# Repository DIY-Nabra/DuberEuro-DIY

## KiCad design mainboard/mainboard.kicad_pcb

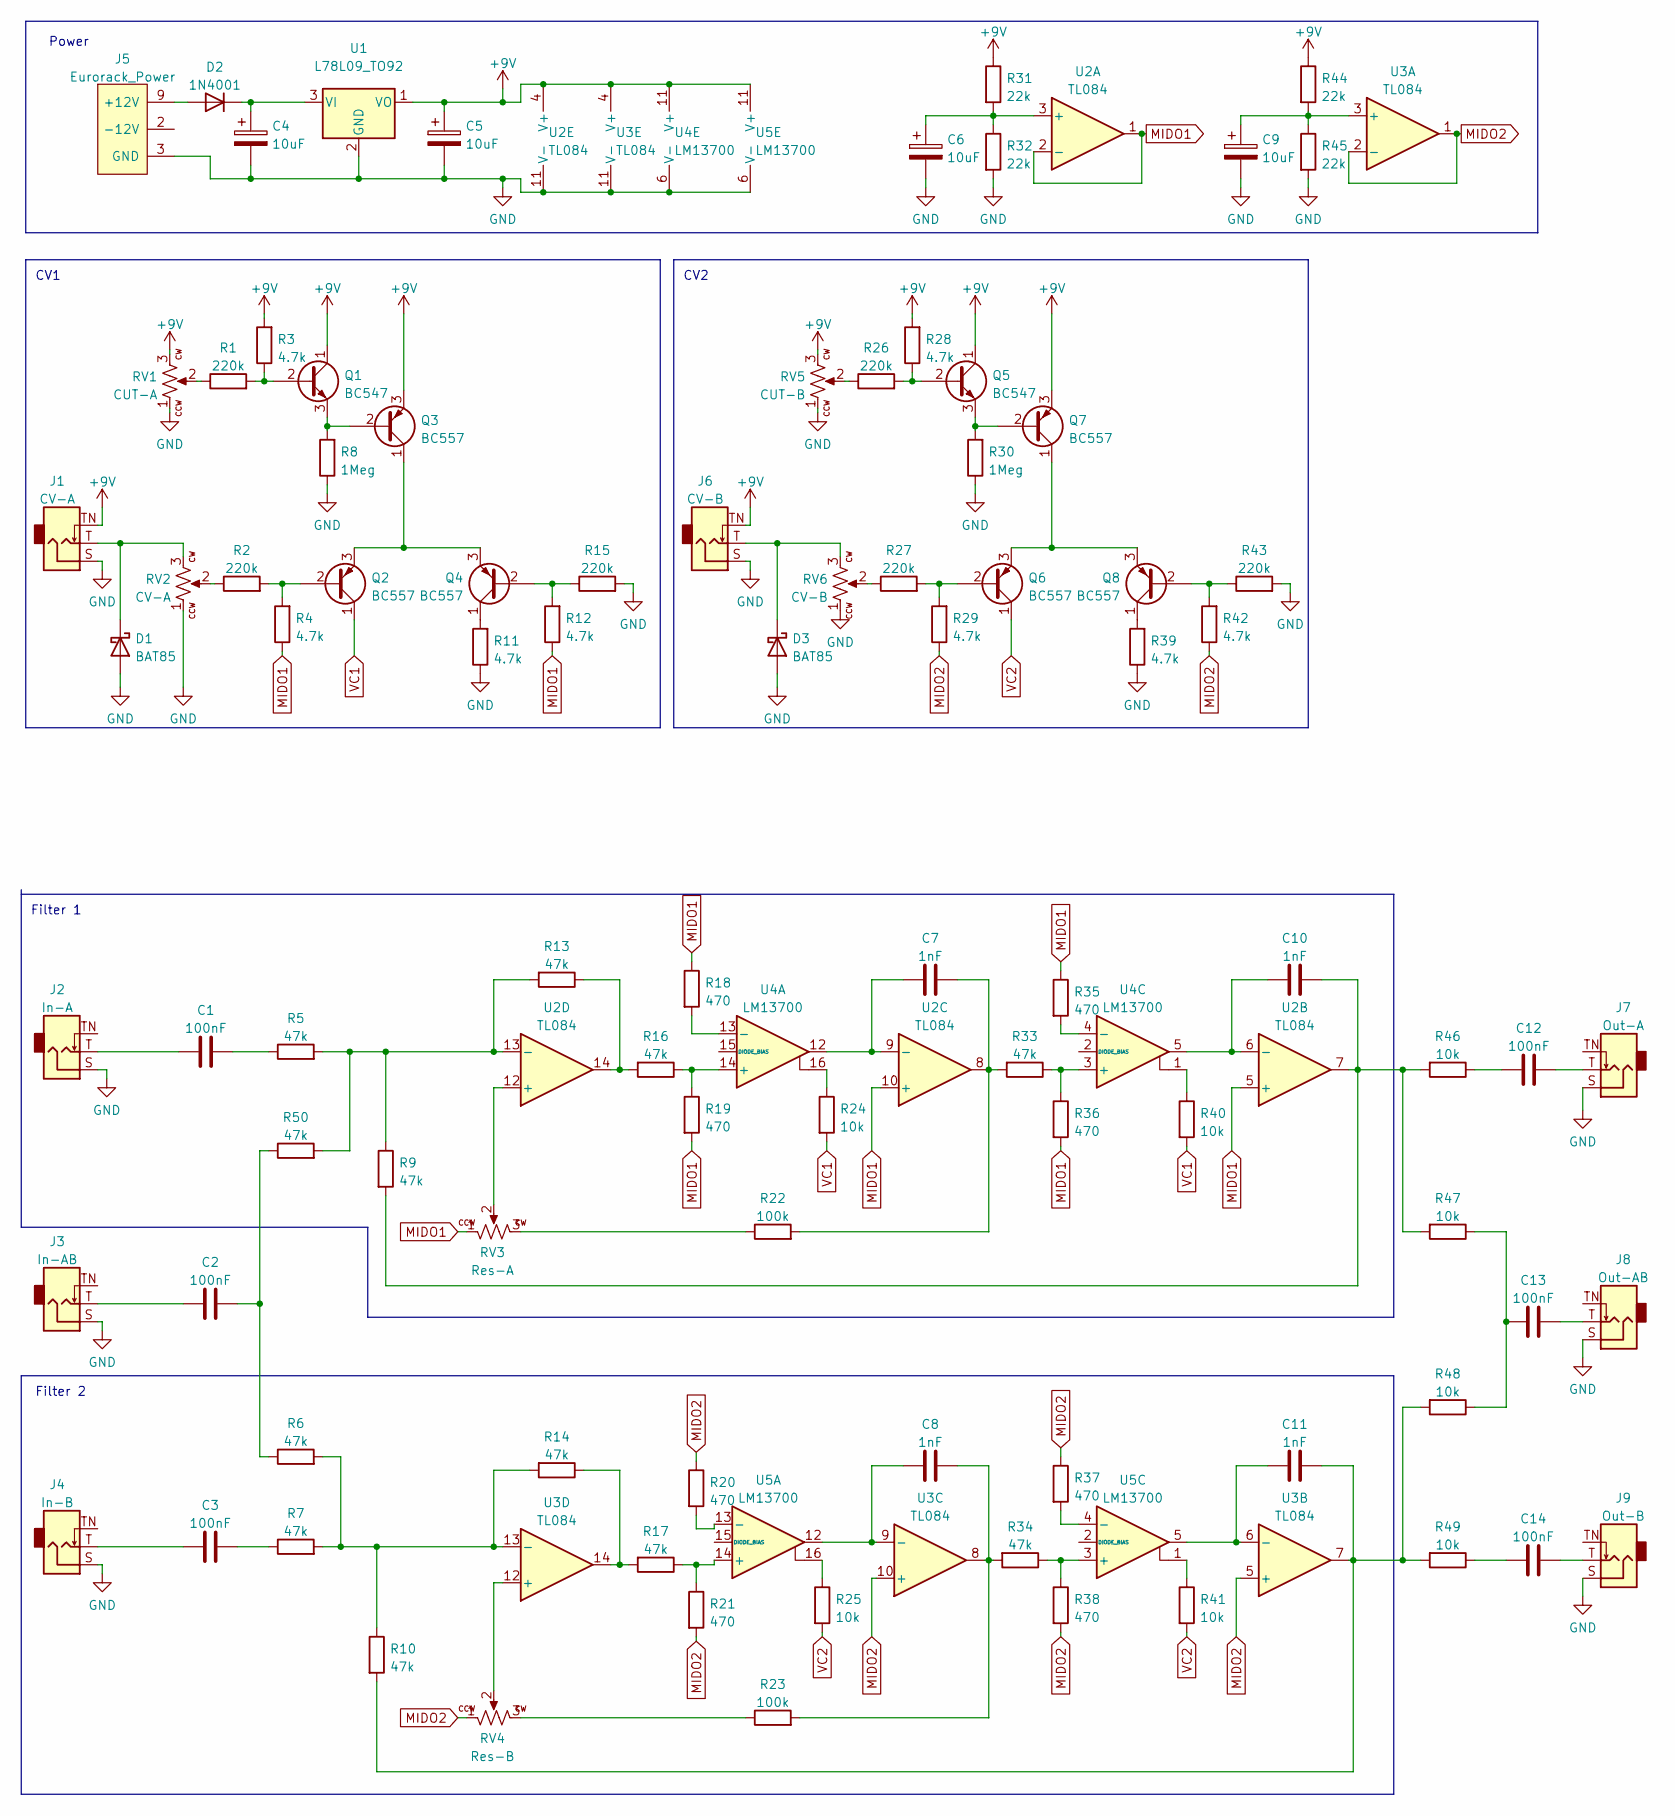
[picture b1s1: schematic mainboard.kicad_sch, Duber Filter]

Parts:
C1, C2, C3, C12, C13, C14: 100nF; C_Axial_L3.8mm_D2.6mm_P7.50mm_Horizontal
C4, C5, C6, C9: 10uF; CP_Radial_D5.0mm_P2.50mm
C7, C8, C10, C11: 1nF; C_Disc_D5.0mm_W2.5mm_P5.00mm
D1, D3: BAT85; D_DO-35_SOD27_P7.62mm_Horizontal
D2: 1N4001; D_DO-41_SOD81_P10.16mm_Horizontal
J1: CV-A; AudioJack_WQP518MA; MPN WQP-WQP518MA
J2: In-A; AudioJack_WQP518MA; MPN WQP-WQP518MA
J3: In-AB; AudioJack_WQP518MA; MPN WQP-WQP518MA
J4: In-B; AudioJack_WQP518MA; MPN WQP-WQP518MA
J5: Eurorack_Power; Eurorack_Power_2x5_Shrouded; MPN 302-S101
J6: CV-B; AudioJack_WQP518MA; MPN WQP-WQP518MA
J7: Out-A; AudioJack_WQP518MA; MPN WQP-WQP518MA
J8: Out-AB; AudioJack_WQP518MA; MPN WQP-WQP518MA
J9: Out-B; AudioJack_WQP518MA; MPN WQP-WQP518MA
Q1, Q5: BC547; TO-92_Inline
Q2, Q3, Q4, Q6, Q7, Q8: BC557; TO-92_Inline
R1, R2, R15, R26, R27, R43: 220k; R_Axial_DIN0204_L3.6mm_D1.6mm_P7.62mm_Horizontal
R3, R4, R11, R12, R28, R29, R39, R42: 4.7k; R_Axial_DIN0204_L3.6mm_D1.6mm_P7.62mm_Horizontal
R5, R6, R7, R9, R10, R13, R14, R16, R17, R33, R34, R50: 47k; R_Axial_DIN0204_L3.6mm_D1.6mm_P7.62mm_Horizontal
R8, R30: 1Meg; R_Axial_DIN0204_L3.6mm_D1.6mm_P7.62mm_Horizontal
R18, R19, R20, R21, R35, R36, R37, R38: 470; R_Axial_DIN0204_L3.6mm_D1.6mm_P7.62mm_Horizontal
R22, R23: 100k; R_Axial_DIN0204_L3.6mm_D1.6mm_P7.62mm_Horizontal
R24, R25, R40, R41, R46, R47, R48, R49: 10k; R_Axial_DIN0204_L3.6mm_D1.6mm_P7.62mm_Horizontal
R31, R32, R44, R45: 22k; R_Axial_DIN0204_L3.6mm_D1.6mm_P7.62mm_Horizontal
RV1: CUT-A; Potentiometer_Alpha_R0904N; MPN R0904N-???? L-25KQ/LWS
RV2: CV-A; Potentiometer_Alpha_R0904N; MPN R0904N-???? L-25KQ/LWS
RV3: Res-A; Potentiometer_Alpha_R0904N; MPN R0904N-???? L-25KQ/LWS
RV4: Res-B; Potentiometer_Alpha_R0904N; MPN R0904N-???? L-25KQ/LWS
RV5: CUT-B; Potentiometer_Alpha_R0904N; MPN R0904N-???? L-25KQ/LWS
RV6: CV-B; Potentiometer_Alpha_R0904N; MPN R0904N-???? L-25KQ/LWS
U1: L78L09_TO92; TO-92_Inline
U2, U3: TL084; DIP-14_W7.62mm_Socket
U4, U5: LM13700; DIP-16_W7.62mm_Socket

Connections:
+9V: C5.1, J1.TN (Tip_normalize), J6.TN (Tip_normalize), Q1.1 (C), Q3.3 (E), Q5.1 (C), Q7.3 (E), R3.2, R28.2, R31.1, R44.1, RV1.3, RV5.3, U1.1 (VO), U2.4 (V+), U3.4 (V+), U4.11 (V+), U5.11 (V+)
GND: C4.2, C5.2, C6.2, C9.2, D1.2 (A), D3.2 (A), J1.S (Sleeve), J2.S (Sleeve), J3.S (Sleeve), J4.S (Sleeve), J5.3 (GND), J5.4 (GND), J5.5 (GND), J5.6 (GND), J5.7 (GND), J5.8 (GND), J6.S (Sleeve), J7.S (Sleeve), J8.S (Sleeve), J9.S (Sleeve), R8.1, R11.1, R15.2, R30.1, R32.2, R39.1, R43.2, R45.2, RV1.1, RV2.1, RV5.1, RV6.1, U1.2 (GND), U2.11 (V-), U3.11 (V-), U4.6 (V-), U5.6 (V-)
MIDO1: R4.1, R12.1, R18.1, R19.2, R35.1, R36.2, RV3.1, U2.1, U2.2 (-), U2.5 (+), U2.10 (+)
MIDO2: R20.1, R21.2, R29.1, R37.1, R38.2, R42.1, RV4.1, U3.1, U3.2 (-), U3.5 (+), U3.10 (+)
unnamed: C1.1, J2.T (Tip)
unnamed: C1.2, R5.1
unnamed: C2.1, J3.T (Tip)
unnamed: C2.2, R6.1, R50.1
unnamed: C3.1, J4.T (Tip)
unnamed: C3.2, R7.1
unnamed: C4.1, D2.1 (K), U1.3 (VI)
unnamed: C6.1, R31.2, R32.1, U2.3 (+)
unnamed: C7.1, U2.9 (-), U4.12
unnamed: C7.2, R22.2, R33.2, U2.8
unnamed: C8.1, U3.9 (-), U5.12
unnamed: C8.2, R23.2, R34.2, U3.8
unnamed: C9.1, R44.2, R45.1, U3.3 (+)
unnamed: C10.1, U2.6 (-), U4.5
unnamed: C10.2, R9.2, R46.2, R47.2, U2.7
unnamed: C11.1, U3.6 (-), U5.5
unnamed: C11.2, R10.2, R48.2, R49.2, U3.7
unnamed: C12.1, R46.1
unnamed: C12.2, J7.T (Tip)
unnamed: C13.1, R47.1, R48.1
unnamed: C13.2, J8.T (Tip)
unnamed: C14.1, R49.1
unnamed: C14.2, J9.T (Tip)
unnamed: D1.1 (K), J1.T (Tip), RV2.3
unnamed: D2.2 (A), J5.9 (+12V), J5.10 (+12V)
unnamed: D3.1 (K), J6.T (Tip), RV6.3
unnamed: J5.1 (-12V), J5.2 (-12V)
unnamed: Q1.2 (B), R1.2, R3.1
unnamed: Q1.3 (E), Q3.2 (B), R8.2
unnamed: Q2.2 (B), R2.2, R4.2
unnamed: Q2.3 (E), Q3.1 (C), Q4.3 (E)
unnamed: Q4.1 (C), R11.2
unnamed: Q4.2 (B), R12.2, R15.1
unnamed: Q5.2 (B), R26.2, R28.1
unnamed: Q5.3 (E), Q7.2 (B), R30.2
unnamed: Q6.2 (B), R27.2, R29.2
unnamed: Q6.3 (E), Q7.1 (C), Q8.3 (E)
unnamed: Q8.1 (C), R39.2
unnamed: Q8.2 (B), R42.2, R43.1
unnamed: R1.1, RV1.2
unnamed: R2.1, RV2.2
unnamed: R6.2, R7.2, R10.1, R14.2, U3.13 (-)
unnamed: R13.1, R16.2, U2.14
unnamed: R5.2, R9.1, R13.2, R50.2, U2.13 (-)
unnamed: R14.1, R17.2, U3.14
unnamed: R16.1, R19.1, U4.14 (+)
unnamed: R17.1, R21.1, U5.14 (+)
unnamed: R18.2, U4.13 (-)
unnamed: R20.2, U5.13 (-)
unnamed: R22.1, RV3.3
unnamed: R23.1, RV4.3
unnamed: R24.1, U4.16
unnamed: R25.1, U5.16
unnamed: R26.1, RV5.2
unnamed: R27.1, RV6.2
unnamed: R33.1, R36.1, U4.3 (+)
unnamed: R34.1, R38.1, U5.3 (+)
unnamed: R35.2, U4.4 (-)
unnamed: R37.2, U5.4 (-)
unnamed: R40.1, U4.1
unnamed: R41.1, U5.1
unnamed: RV3.2, U2.12 (+)
unnamed: RV4.2, U3.12 (+)
VC1: Q2.1 (C), R24.2, R40.2
VC2: Q6.1 (C), R25.2, R41.2

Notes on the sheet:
CV1
Filter 2
Power
Filter 1
CV2

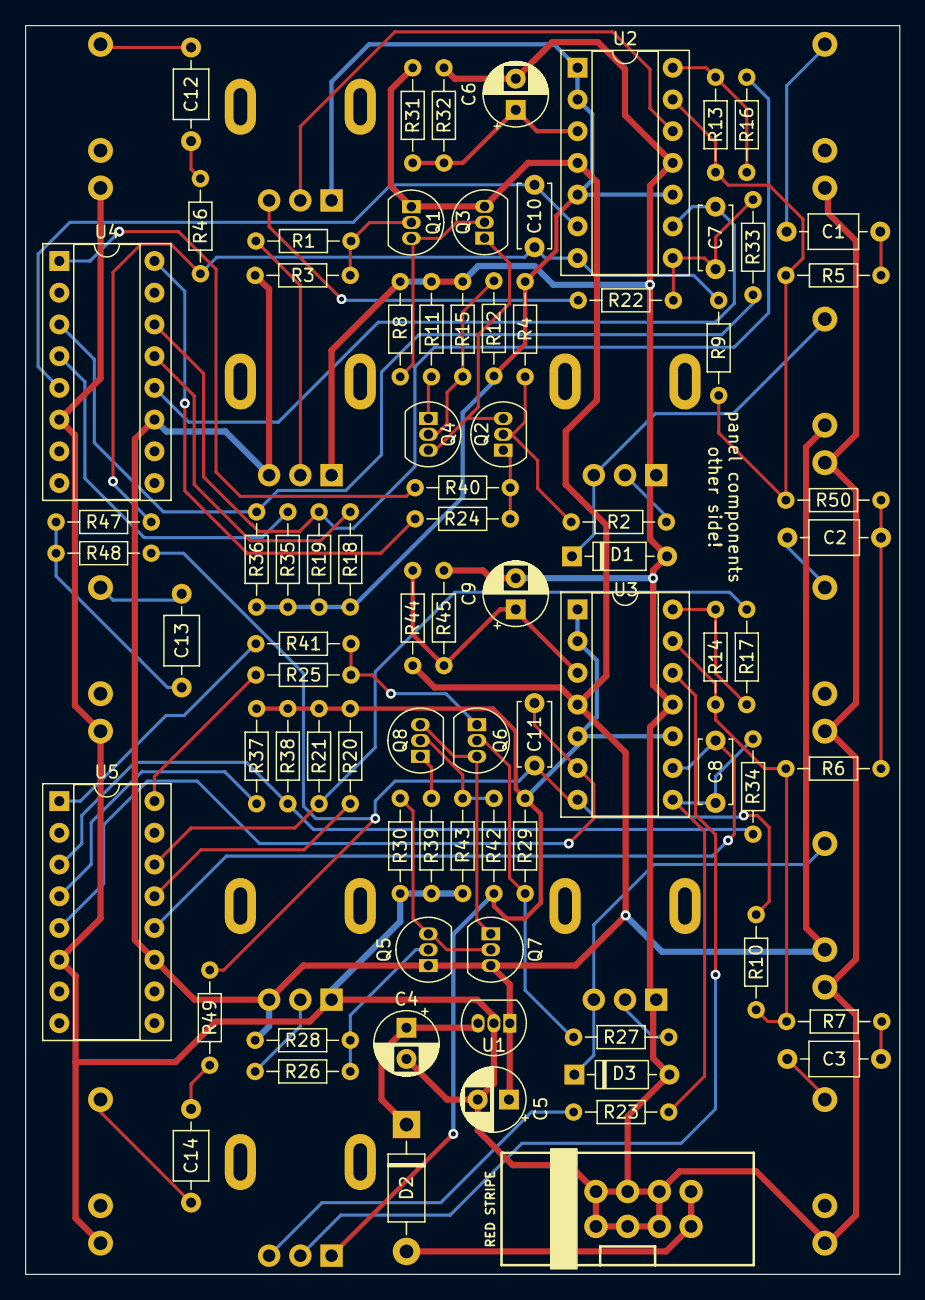
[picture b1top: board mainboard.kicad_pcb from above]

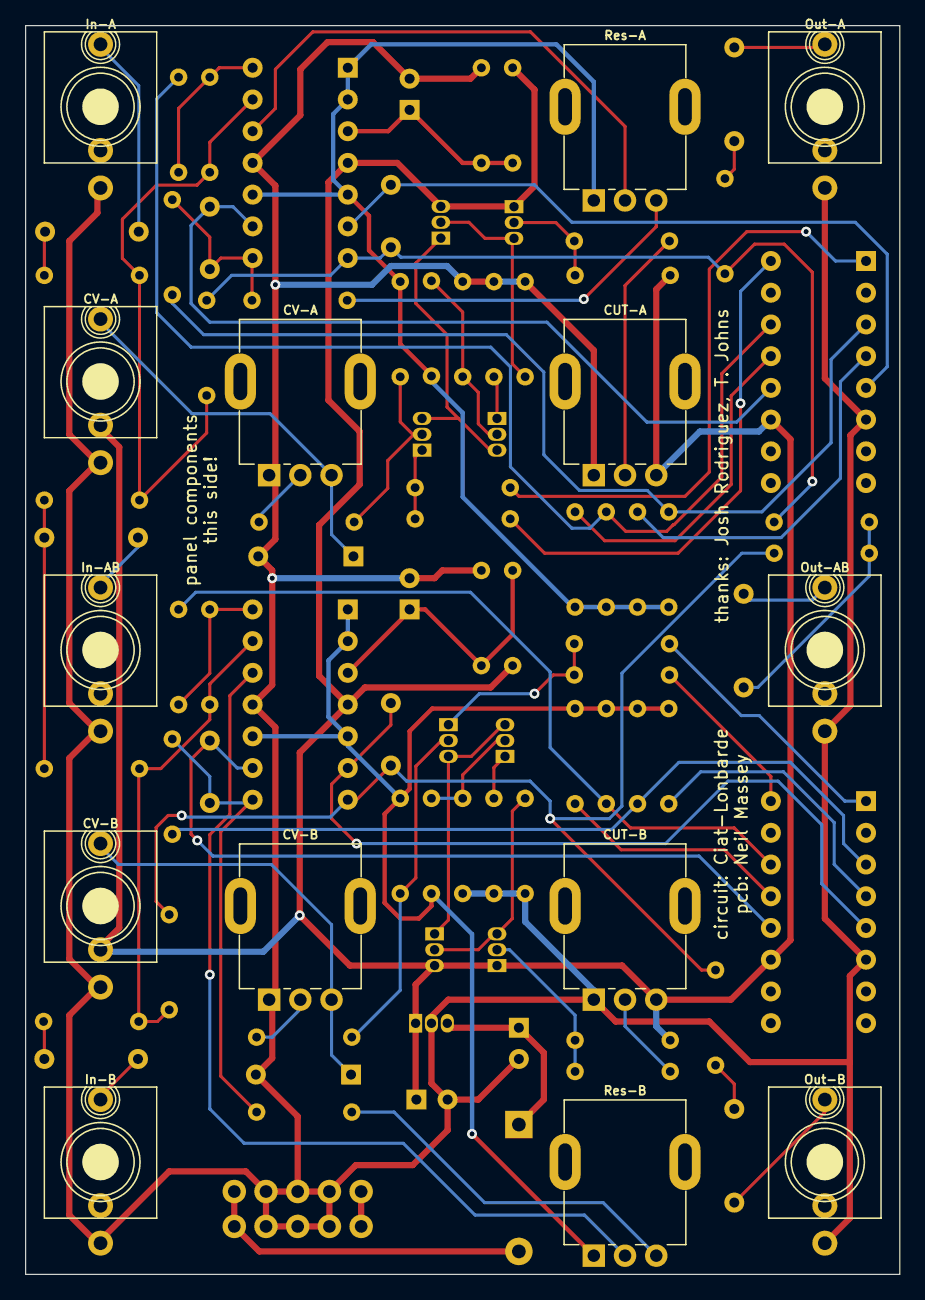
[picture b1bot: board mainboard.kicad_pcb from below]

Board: 2 copper layers, 70.0 x 100.0 mm, 95 parts (14 on the bottom side), 69 nets.

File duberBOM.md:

# Duber Bill of Materials (BOM)

To build just follow the order in the BOM.

When soldering the ICs (U2->U5), solder in the equivalent sockets instead.

Solder the panel components (jacks and pots) last, on the opposite side of the board to the other parts.

| Reference | Quantity | Part | Notes |
|-----------|----------|------|-------|
| R46,R47,R48,R49 | 4 | 1k or 10k | Output resistor |
| R24,R25,R40,R41 | 4 | 10k | |
| R22,R23 | 2 | 100k | |
| R8,R30 | 2 | 1M | |
| R31,R32,R44,R45 | 4 | 22k | |
| R1,R2,R15,R26,R27,R43 | 6 | 220k | |
| R18,R19,R20,R21,R35,R36,R37,R38| 8 | 470R | |
| R3,R4,R11,R12,R28,R29,R39,R42 | 8 | 4.7k | |
| R5,R6,R7,R9,R10,R13,R14,R16,R17,R33,R34,R50 | 12 | 47k | |
| D1,D3 | 2 | BAT85 | Negative voltage protection diodes |
| D2 | 1 | 1N4001 | Reverse voltage protection diode |
| C1,C2,C3,C12,C13,C14 | 6 | 100nF | Mylar or MLCC, audio path |
| C4,C5,C6,C9 | 4 | 10uF Electrolytic | Power conditioning caps |
| C10,C8,C11,C7 | 4 | 1nF | Mylar or MLCC |
| Q2,Q3,Q4,Q6,Q7,Q8 | 6 | BC557 | |
| Q1,Q5 | 2 | BC547 | TO92 |
| U1 | 1 | L78L09 TO92 | Power regulator |
| U2,U3 | 2 | TL084 | Or use TL074 |
| U4,U5 | 2 | LM13700 | |
| J5 | 1 | Eurorack 2x5 shrouded male | |
| RV1,RV2,RV3,RV4,RV5,RV6 | 6 | 10k 9mm potentiometer | |
| J1,J2,J3,J4,J6,J7,J8,J9 | 8 | Thonkiconn 3.5mm mono socket | |
| IC socket 14 pin | 2 | DIP 14 pin socket | |
| IC socket 16 pin | 2 | DIP 16 pin socket | |

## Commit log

2022-08-03 First commit of KiCad implementation of Vaux Flores interpretation of the Duber filter
2022-08-19 Schematic
2022-08-25 Panel and trace corrections
2022-08-25 Removed DS_Store
2022-08-25 added mainboard.kicad_prl
2022-08-26 Panel tweak
2022-08-26 Panel tweaks
2022-08-26 Added LICENSE
2022-08-26 Added LICENSE summary
2022-08-26 Markdown formatting
2022-08-26 Added BOM
2022-08-27 nologo panel and branch
2022-09-03 updated BOM, some layout tweaks
